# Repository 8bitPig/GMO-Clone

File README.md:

# GMO-Clone
a non commercial clone of the Moffenzeef GMO

I am not related to Moffenzeef Modular Company. 
They are not related to the files shared here but allowed me to share them. 

Moffenzeef will NOT do any SUPPORT for this!!! Please do not ask them for help! 

Please do NOT ever SELL the DIY Module you built. 
(CC-BY-NC-SA 4.0)

Before ordering, the files, especially the schemantic should be checked for errors or missing connections by a second pair of eyes please. If you checked them, please let me know. :)

built and tested this version sucessfully on 24th of august 2019.

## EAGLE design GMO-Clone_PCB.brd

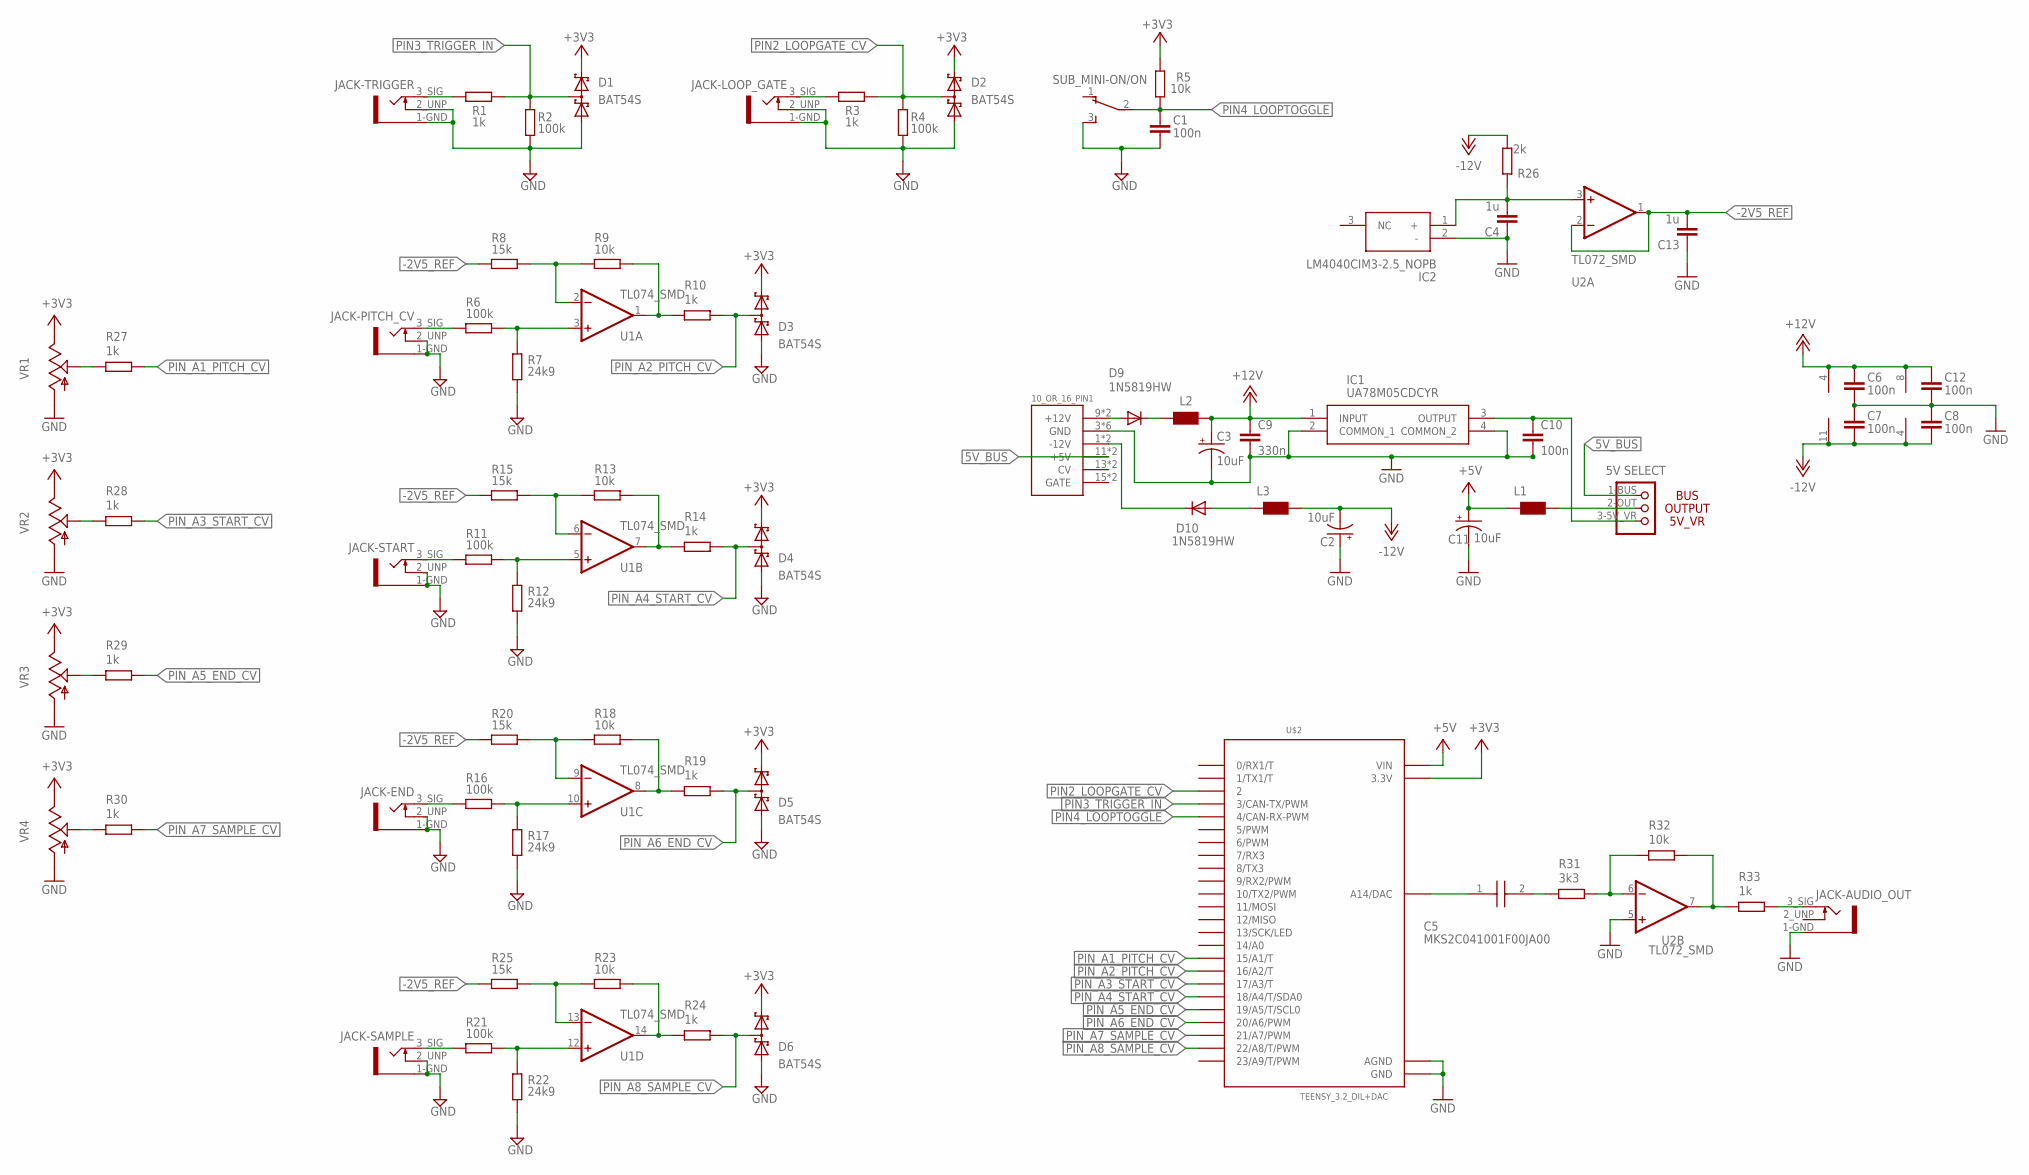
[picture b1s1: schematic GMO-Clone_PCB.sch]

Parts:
10_OR_16_PIN1: POWER; POWER_16
C1, C6, C7, C8, C12: 100n; C0603K
C2, C3, C11: 10uF; PANASONIC_D
C4, C13: 1u; C0603
C5: MKS2C041001F00JA00
C9: 330n; C0603
C10: 100n; C0603
D1, D2, D3, D4, D5, D6: BAT54S; SOT23
D9, D10: 1N5819HW; DIODE_SOD123
IC1: UA78M05CDCYR; SOT230P700X180-4N
IC2: LM4040CIM3-2.5_NOPB; SOT95P237X112-3N
JACK-AUDIO_OUT: MISC_JACKTHONK_PJ301M-12; THONK_PJ301M-12
JACK-END: MISC_JACKTHONK_PJ301M-12; THONK_PJ301M-12
JACK-LOOP_GATE: MISC_JACKTHONK_PJ301M-12; THONK_PJ301M-12
JACK-PITCH_CV: MISC_JACKTHONK_PJ301M-12; THONK_PJ301M-12
JACK-SAMPLE: MISC_JACKTHONK_PJ301M-12; THONK_PJ301M-12
JACK-START: MISC_JACKTHONK_PJ301M-12; THONK_PJ301M-12
JACK-TRIGGER: MISC_JACKTHONK_PJ301M-12; THONK_PJ301M-12
JP2: SELECTOR_POWER
L1, L2, L3: WE-CBF_0603; 0603
R1, R3, R10, R14, R19, R24, R27, R28, R29, R30, R33: 1k; R0603
R2, R4, R6, R11, R16, R21: 100k; R0603
R5, R9, R13, R18, R23, R32: 10k; R0603
R7, R12, R17, R22: 24k9; R0603
R8, R15, R20, R25: 15k; R0603
R26: 2k; R0603
R31: 3k3; R0603
SUB_MINI-ON/ON: TL36PO; TL3XPO
U1: TL074_SMD; SO14
U2: TL072_SMD; SO08
U$2: TEENSY_3.2_DIL+DAC
VR1, VR2, VR3, VR4: 9MM_SNAP-IN_POT_; 9MM_SNAP-IN_POT

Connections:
5V_BUS: 10_OR_16_PIN1.11 (+5V), 10_OR_16_PIN1.12 (+5V), JP2.1-BUS
+3V3: D1.2 (C2), D2.2 (C2), D3.2 (C2), D4.2 (C2), D5.2 (C2), D6.2 (C2), R5.2, U$2.3.3V, VR1.3 (E), VR2.3 (E), VR3.3 (E), VR4.3 (E)
+5V: C11.+, L1.1, U$2.VIN
+12V: C3.+, C6.1, C9.1, C12.1, IC1.1 (INPUT), L2.2, U1.4 (V+), U2.8 (V+)
-2V5_REF: C13.2, R8.1, R15.1, R20.1, R25.1, U2.1 (OUT), U2.2 (-IN)
-12V: C2.-, C7.2, C8.2, L3.2, R26.2, U1.11 (V-), U2.4 (V-)
GND: 10_OR_16_PIN1.3 (GND), 10_OR_16_PIN1.4 (GND), 10_OR_16_PIN1.5 (GND), 10_OR_16_PIN1.6 (GND), 10_OR_16_PIN1.7 (GND), 10_OR_16_PIN1.8 (GND), C1.2, C2.+, C3.-, C4.1, C6.2, C7.1, C8.1, C9.2, C10.2, C11.-, C12.2, C13.1, D1.1 (A1), D2.1 (A1), D3.1 (A1), D4.1 (A1), D5.1 (A1), D6.1 (A1), IC1.2 (COMMON_1), IC1.4 (COMMON_2), IC2.2 (-), JACK-AUDIO_OUT.1-GND, JACK-END.1-GND, JACK-END.2_UNP (2-UNPLUGGED), JACK-LOOP_GATE.1-GND, JACK-LOOP_GATE.2_UNP (2-UNPLUGGED), JACK-PITCH_CV.1-GND, JACK-PITCH_CV.2_UNP (2-UNPLUGGED), JACK-SAMPLE.1-GND, JACK-SAMPLE.2_UNP (2-UNPLUGGED), JACK-START.1-GND, JACK-START.2_UNP (2-UNPLUGGED), JACK-TRIGGER.1-GND, JACK-TRIGGER.2_UNP (2-UNPLUGGED), R2.1, R4.1, R7.1, R12.1, R17.1, R22.1, SUB_MINI-ON/ON.3 (S), U2.5 (+IN), U$2.AGND, U$2.GND, VR1.1 (A), VR2.1 (A), VR3.1 (A), VR4.1 (A)
unnamed: JACK-LOOP_GATE.3_SIG (3-SIGNAL_IN_OUT), R3.1
unnamed: JACK-TRIGGER.3_SIG (3-SIGNAL_IN_OUT), R1.1
unnamed: JACK-PITCH_CV.3_SIG (3-SIGNAL_IN_OUT), R6.1
unnamed: R9.1, R10.2, U1.1 (OUT)
unnamed: R8.2, R9.2, U1.2 (-IN)
unnamed: JACK-START.3_SIG (3-SIGNAL_IN_OUT), R11.1
unnamed: R6.2, R7.2, U1.3 (+IN)
unnamed: R13.1, R14.2, U1.7 (OUT)
unnamed: R13.2, R15.2, U1.6 (-IN)
unnamed: R11.2, R12.2, U1.5 (+IN)
unnamed: JACK-END.3_SIG (3-SIGNAL_IN_OUT), R16.1
unnamed: R18.1, R19.2, U1.8 (OUT)
unnamed: R18.2, R20.2, U1.9 (-IN)
unnamed: R16.2, R17.2, U1.10 (+IN)
unnamed: JACK-SAMPLE.3_SIG (3-SIGNAL_IN_OUT), R21.1
unnamed: R23.1, R24.2, U1.14 (OUT)
unnamed: R23.2, R25.2, U1.13 (-IN)
unnamed: R21.2, R22.2, U1.12 (+IN)
unnamed: R27.2, VR1.2 (S)
unnamed: R28.2, VR2.2 (S)
unnamed: R29.2, VR3.2 (S)
unnamed: R30.2, VR4.2 (S)
unnamed: C10.1, IC1.3 (OUTPUT), JP2.3-5V_VR (3-VR)
unnamed: 10_OR_16_PIN1.9 (+12V), 10_OR_16_PIN1.10 (+12V), D9.A
unnamed: C5.1, U$2.RESET/DAC (A14/DAC)
unnamed: 10_OR_16_PIN1.1 (-12V), 10_OR_16_PIN1.2 (-12V), D10.C
unnamed: C4.2, IC2.1 (+), R26.1, U2.3 (+IN)
unnamed: C5.2, R31.2
unnamed: R31.1, R32.2, U2.6 (-IN)
unnamed: R32.1, R33.2, U2.7 (OUT)
unnamed: JACK-AUDIO_OUT.3_SIG (3-SIGNAL_IN_OUT), R33.1
unnamed: JP2.2-OUT, L1.2
unnamed: D9.C, L2.1
unnamed: D10.A, L3.1
PIN2_LOOPGATE_CV: D2.3 (C1A2), R3.2, R4.2, U$2.2
PIN3_TRIGGER_IN: D1.3 (C1A2), R1.2, R2.2, U$2.3 (3/CAN-TX/PWM)
PIN4_LOOPTOGGLE: C1.1, R5.1, SUB_MINI-ON/ON.2, U$2.4 (4/CAN-RX-PWM)
PIN_A1_PITCH_CV: R27.1, U$2.15/A1 (15/A1/T)
PIN_A2_PITCH_CV: D3.3 (C1A2), R10.1, U$2.16/A2 (16/A2/T)
PIN_A3_START_CV: R28.1, U$2.17/A3 (17/A3/T)
PIN_A4_START_CV: D4.3 (C1A2), R14.1, U$2.18/A4 (18/A4/T/SDA0)
PIN_A5_END_CV: R29.1, U$2.19/A5 (19/A5/T/SCL0)
PIN_A6_END_CV: D5.3 (C1A2), R19.1, U$2.20/A6 (20/A6/PWM)
PIN_A7_SAMPLE_CV: R30.1, U$2.21/A7 (21/A7/PWM)
PIN_A8_SAMPLE_CV: D6.3 (C1A2), R24.1, U$2.22/A8 (22/A8/T/PWM)

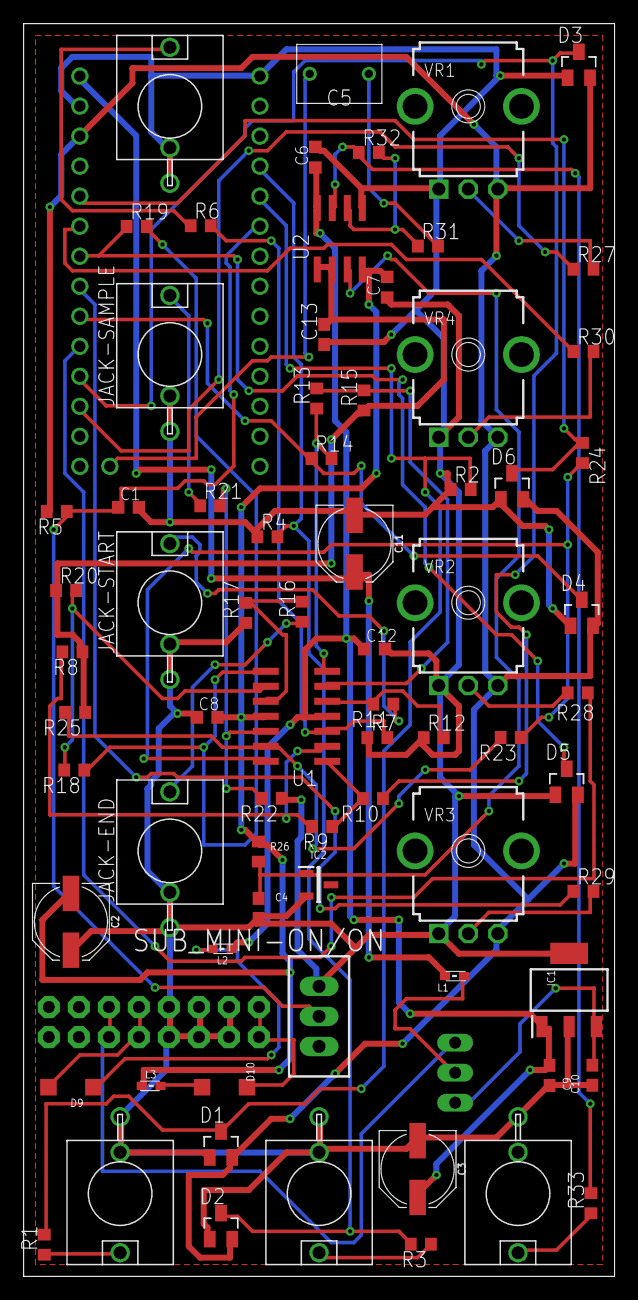
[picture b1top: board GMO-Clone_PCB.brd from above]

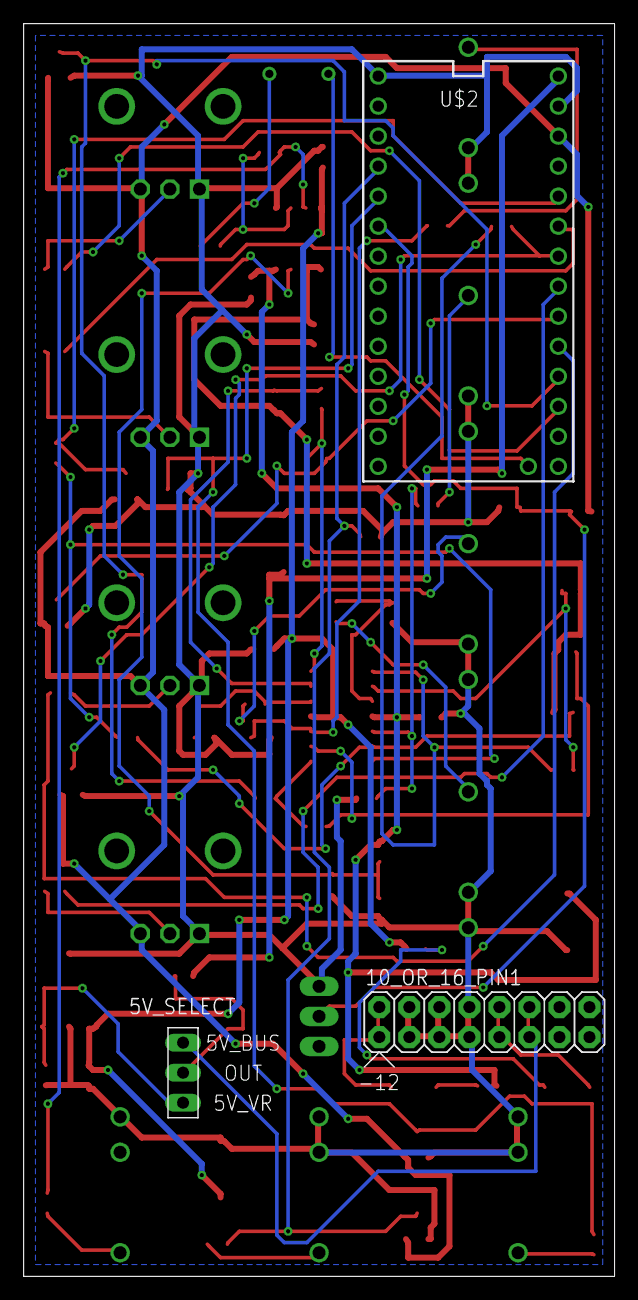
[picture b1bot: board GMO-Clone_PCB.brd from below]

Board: 2 copper layers, 50.0 x 106.0 mm, 76 parts (3 on the bottom side), 52 nets.

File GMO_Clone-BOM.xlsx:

Qty | Value | Device | Package | Parts | Description | DESCRIPTION2 | HEIGHT | MANUFACTURER_NAME | MANUFACTURER_PART_NUMBER | MOUSER_PART_NUMBER | MOUSER_PRICE-STOCK | PROD_ID | RS_PART_NUMBER | RS_PRICE-STOCK | VALUE3
4 |  | 9MM_SNAP-IN_POT_ | 9MM_SNAP-IN_POT | VR1, VR2, VR3, VR4 | 9mm vertical snap-in pot, Alpha / Panasonic style
1 |  | SELECTOR_POWER | SELECTOR_POWER | JP2 | PIN HEADER
3 |  | WE-CBF_0603 | 603 | L1, L2, L3 | SMD EMI Suppression Ferrite Beads
6 | 100k | R-EU_R0603 | R0603 | R2, R4, R6, R11, R16, R21 | RESISTOR, European symbol
1 | 100n | C-EUC0603 | C0603 | C10 | CAPACITOR, European symbol
5 | 100n | C-EUC0603K | C0603K | C1, C6, C7, C8, C12 | CAPACITOR, European symbol
6 | 10k | R-EU_R0603 | R0603 | R5, R9, R13, R18, R23, R32 | RESISTOR, European symbol
3 | 10uF | 47UF-POLAR-PANASONIC_D-35V-20% | PANASONIC_D | C2, C3, C11 | 47ÂµF polarized capacitors |  |  |  |  |  |  | CAP-08478 |  |  | 47uF
4 | 15k | R-EU_R0603 | R0603 | R8, R15, R20, R25 | RESISTOR, European symbol
2 | 1N5819HW | DIODE_DIODE-SOD123 | DIODE_SOD123 | D9, D10 | DIODE
11 | 1k | R-EU_R0603 | R0603 | R1, R3, R10, R14, R19, R24, R27, R28, R29, R30, R33 | RESISTOR, European symbol
2 | 1u | C-EUC0603 | C0603 | C4, C13 | CAPACITOR, European symbol
4 | 24k9 | R-EU_R0603 | R0603 | R7, R12, R17, R22 | RESISTOR, European symbol
1 | 2k | R-EU_R0603 | R0603 | R26 | RESISTOR, European symbol
1 | 330n | C-EUC0603 | C0603 | C9 | CAPACITOR, European symbol
1 | 3k3 | R-EU_R0603 | R0603 | R31 | RESISTOR, European symbol
6 | BAT54S | BAT54S | SOT23 | D1, D2, D3, D4, D5, D6 | Schottky Diodes
1 | LM4040CIM3-2.5_NOPB | LM4040CIM3-2.5_NOPB | SOT95P237X112-3N | IC2 | 100-ppm/C precision micropower shunt voltage reference | 100-ppm/C precision micropower shunt voltage reference | 1.12mm | Texas Instruments | LM4040CIM3-2.5/NOPB | 926-LM4040CIM325NOPB | https://www.mouser.com/Search/Refine.aspx?Keyword=926-LM4040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 |  | 5359600P | http://uk.rs-online.com/web/p/products/5359600P
7 | MISC_JACKTHONK_PJ301M-12 | MISC_JACKTHONK_PJ301M-12 | THONK_PJ301M-12 | JACK-AUDIO_OUT, JACK-END, JACK-LOOP_GATE, JACK-PITCH_CV, JACK-SAMPLE, JACK-STAR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 | 3.5mm Mono Switching Jack
1 | MKS2C041001F00JA00 | MKS2C041001F00JA00 | MKS2C041001F00JA00 | C5 | Film Capacitors 1.0 uF 63 VDC 5% | Film Capacitors 1.0 uF 63 VDC 5% | 10mm | WIMA | MKS2C041001F00JA00 | 505-MKS2C041001F00JA | https://www.mouser.com/Search/Refine.aspx?Keyword=505-MKS2C0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
1 | POWER | POWER | POWER_16 | 10_OR_16_PIN1
1 | TEENSY_3.2_DIL+DAC | TEENSY_3.2_DIL+DAC | TEENSY_3.2_DIL+DAC | U$2 | Footprint for Teensy 3.1 or 3.2 board using all pin connections on the outer pe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
1 | TL072_SMD | TL072_SMD | SO08 | U2 | Generic Dual Op Amp
1 | TL074_SMD | TL074_SMD | SO14 | U1 | Generic Quad Op Amp
1 | TL36PO | TL36PO | TL3XPO | SUB_MINI-ON/ON | TINY SWITCH ON - ON
1 | UA78M05CDCYR | UA78M05CDCYR | SOT230P700X180-4N | IC1 | 500-mA, 25-V, Linear Voltage Regulators | 500-mA, 25-V, Linear Voltage Regulators | 1.8mm | Texas Instruments | UA78M05CDCYR | 595-UA78M05CDCYR | https://www.mouser.com/Search/Refine.aspx?Keyword=595-UA78M05CDCYR

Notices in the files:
parts and their libraries:
SparkFun-Capacitors: Licensing: Creative Commons ShareAlike 4.0 International - https://creativecommons.org/licenses/by-sa/4.0
